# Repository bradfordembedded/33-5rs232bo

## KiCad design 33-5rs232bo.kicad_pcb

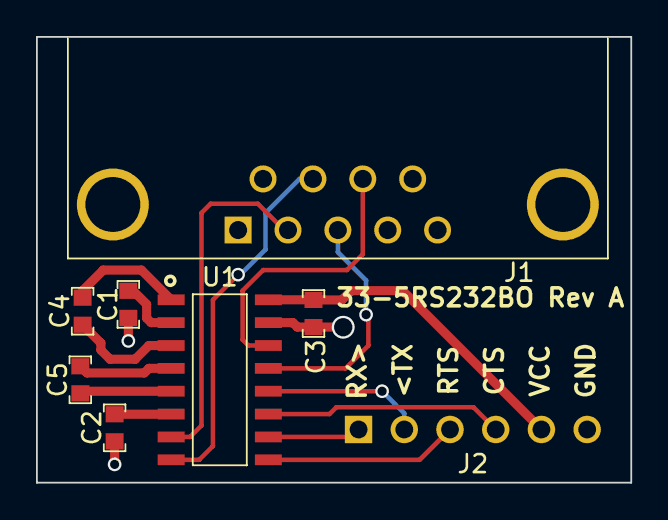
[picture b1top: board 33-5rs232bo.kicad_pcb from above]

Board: 2 copper layers, 33.0 x 24.8 mm, 8 parts (0 on the bottom side), 16 nets.

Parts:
C1, C2, C3, C4, C5: 0.1U; SMT-0603
J1: DB9-RS232; A-DF-09-AKG-T2S
J2: HEADER-6PIN; HEADER-100MIL-6
U1: SP3232EU; SOIC-N-16

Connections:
+3.3V: C3.1, J2.5, U1.16
/CTS: J1.8, U1.14
/CTS-D: J2.4, U1.11
/RTS: J1.7, U1.8
/RTS-D: J2.3, U1.9
/RX: J1.2, U1.7
/RX-D: J2.1, U1.10
/TX: J1.3, U1.13
/TX-D: J2.2, U1.12
GND: C1.2, C2.2, C3.2, J1.5, J2.6, U1.15
unnamed: C4.2, U1.3
unnamed: C5.2, U1.5
unnamed: C5.1, U1.4
unnamed: C1.1, U1.2
unnamed: C4.1, U1.1
unnamed: C2.1, U1.6

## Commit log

2015-04-23 Rev A release!
2015-04-23 Add LICENSE

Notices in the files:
33-5rs232bo.kicad_pcb:
Licensed under the CERN OHL v1.2
